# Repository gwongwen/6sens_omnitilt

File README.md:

# 6Sens: inSitu Seismic System for Slope Stability Sensing

## Desciption
The goal is to develop a warning system on the analysis of the evolution of the micro-seismic activity generated before the instability is triggered. The method uses a multitude of low-cost seismic sensors deployed in-situ in a network over the possibly unstable zone. The goal is to characterize the temporal evolution of seismic signals detected simultaneously by several sensors (i .e., co-detection). This method uses to its advantage the heterogeneity of the materials and the attenuation of the waves during their propagation in the material.

The design of these sensors is subject to certain technical constraints essential to good
operation of the project:

    - Be autonomous in energy, over a period of several months (so as not to have to return to site, often dangerous).
    - Be robust, reliable and adapted to extreme climatic conditions (cold, hot, humidity).
    - All sensors in the network must be synchronized precisely enough to perform the analysis (about 1/10 second).
    - Be able to communicate information in real time – or near – measurements to a gateway that will retransmit the data to a dedicated website.
    - Be produced at low cost (to install a large-scale network, and have the possibility of to install sensors in hazardous areas with the possibility of losing them).

## Hardware description
### Geophone sensor
The choice fell on omni geometric sensors from Geospace Technologies such Omni-X-LT or GS-ONE. Seismic geophone is a type of sensor that converts ground movement or a kind vibration into voltage, which could be acquired by an acquisition system. The deviation of this mesured voltage from the base line is called the geophone response and is analysed and for monitoring vibration generated by nature in our case.

The frequency response of the geophone is a kind of harmonic oscillator, which is deternined by corner frequency, around 15Hz for the chosen sensors and damping (typically 0.7 for our case).
Our application require the full wave to be sued and the three-component 3C geophones is used (Omni-X-LT or GS-ONE).
For more information, please to refer to : https://www.geospace.com/products/sensors/

### Amplification/Filtering board
The specifications inform us about the bandwidth of the filtering to be carried out: from 20Hz at 100Hz. So we have to build a band-pass filter having an amplification almost constant on this band and rejects frequencies outside this band. Moreover, the signal will have to be amplified in order to obtain a complete dynamic range between 0 and 3.3V without saturation. Below are listed the
parameters of the different filters that will make up the amplification and filtering card :

    - Filter 1 : active bandpass filter, gain : 33dB, low frequency : 7Hz, high frequency : 154Hz
    - Filter 2 : passive low-pass filter, no gain, cut frequency : 106Hz
    - Filter 3 : active low-pass filter, gain : 6dB, cut frequency : 234Hz

### CPU/Radio board for test
The choice fell on Cicerone MKR main board. Move-X Cicerone LoRa/GNSS Board is a high-performance, low-power, Arduino MKR-compatible development board based on the MAMWLE LoRa Module and the u-blox MAX-M10S GNSS Module. The Cicerone Board delivers best-in-class GNSS, long-range wireless connection, and high-performance MCU processing in a low-power solution for optimal battery life. The Cicerone Board allows users to build tracking applications worldwide with meter-level accuracy and to communicate long-range, low-power data via LoRaWAN. The integrated Li-Po charging circuit enables the Cicerone Board to manage battery charging through the USB port.

### CPU/Radio board for POC
The choice was made to manufacture our own PCB. It has three parts: the MAMWLE-01 radio chipset to transmit LoRaWAN packets (based on an STM32WLE5jx), a UWB chipset DW1000 to measure distance between two sensors and an analog part to supply radio chipset (solar panel or/and Li-Po battery). Connectors (Arduino MKR-compatible) have also been added to insert the seismic sensor amplification/filtering board.

## Firmware description
For this project, the use of Zephyr RTOS has been retained. To see what is Zephyr RTOS and how to install it on your computer, go to https://docs.zephyrproject.org/latest/develop/getting_started/index.html (it supports Linux OS, Windows OS and macOS).

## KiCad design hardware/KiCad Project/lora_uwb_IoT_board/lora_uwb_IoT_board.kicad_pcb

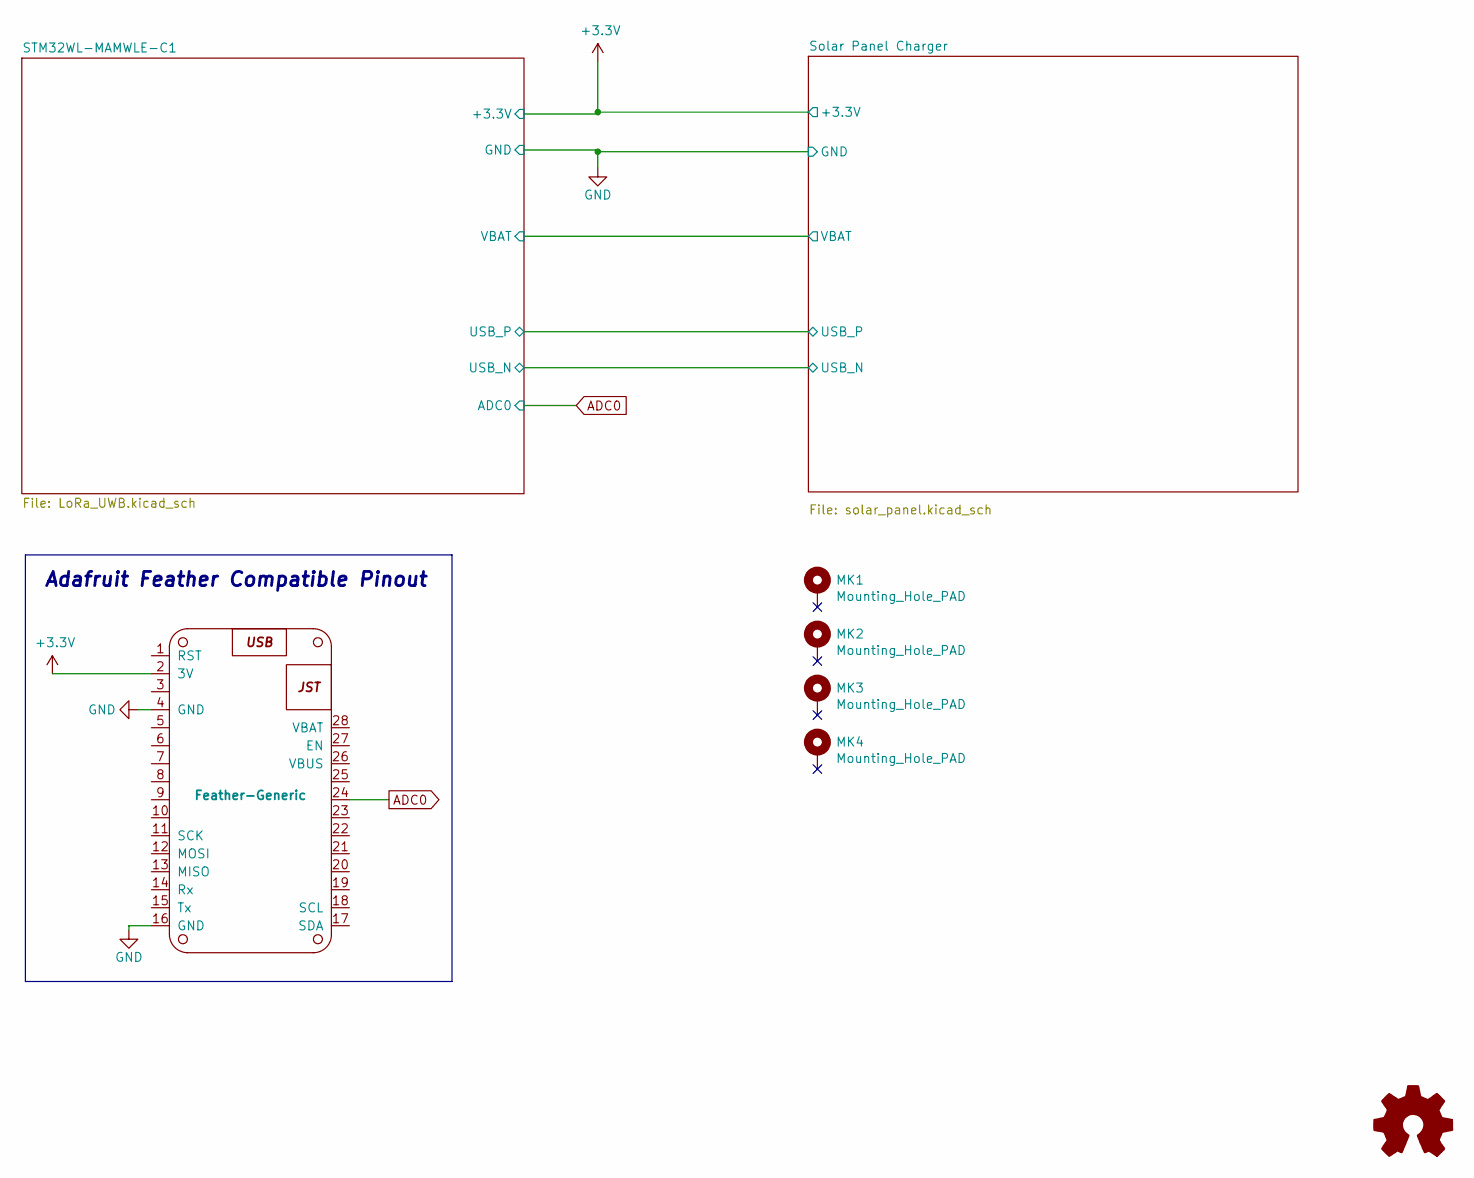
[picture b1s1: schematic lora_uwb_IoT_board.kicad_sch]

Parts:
MK1, MK2, MK3, MK4: Mounting_Hole_PAD; MountingHole_2.7mm
U300: Feather-Generic; Feather-Generic-no-holes

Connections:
+3V3: U300.2 (3V); also elsewhere on the board
ADC0: U300.24; also elsewhere on the board
GND: U300.4 (GND), U300.16 (GND); also elsewhere on the board

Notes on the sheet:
Adafruit Feather Compatible Pinout

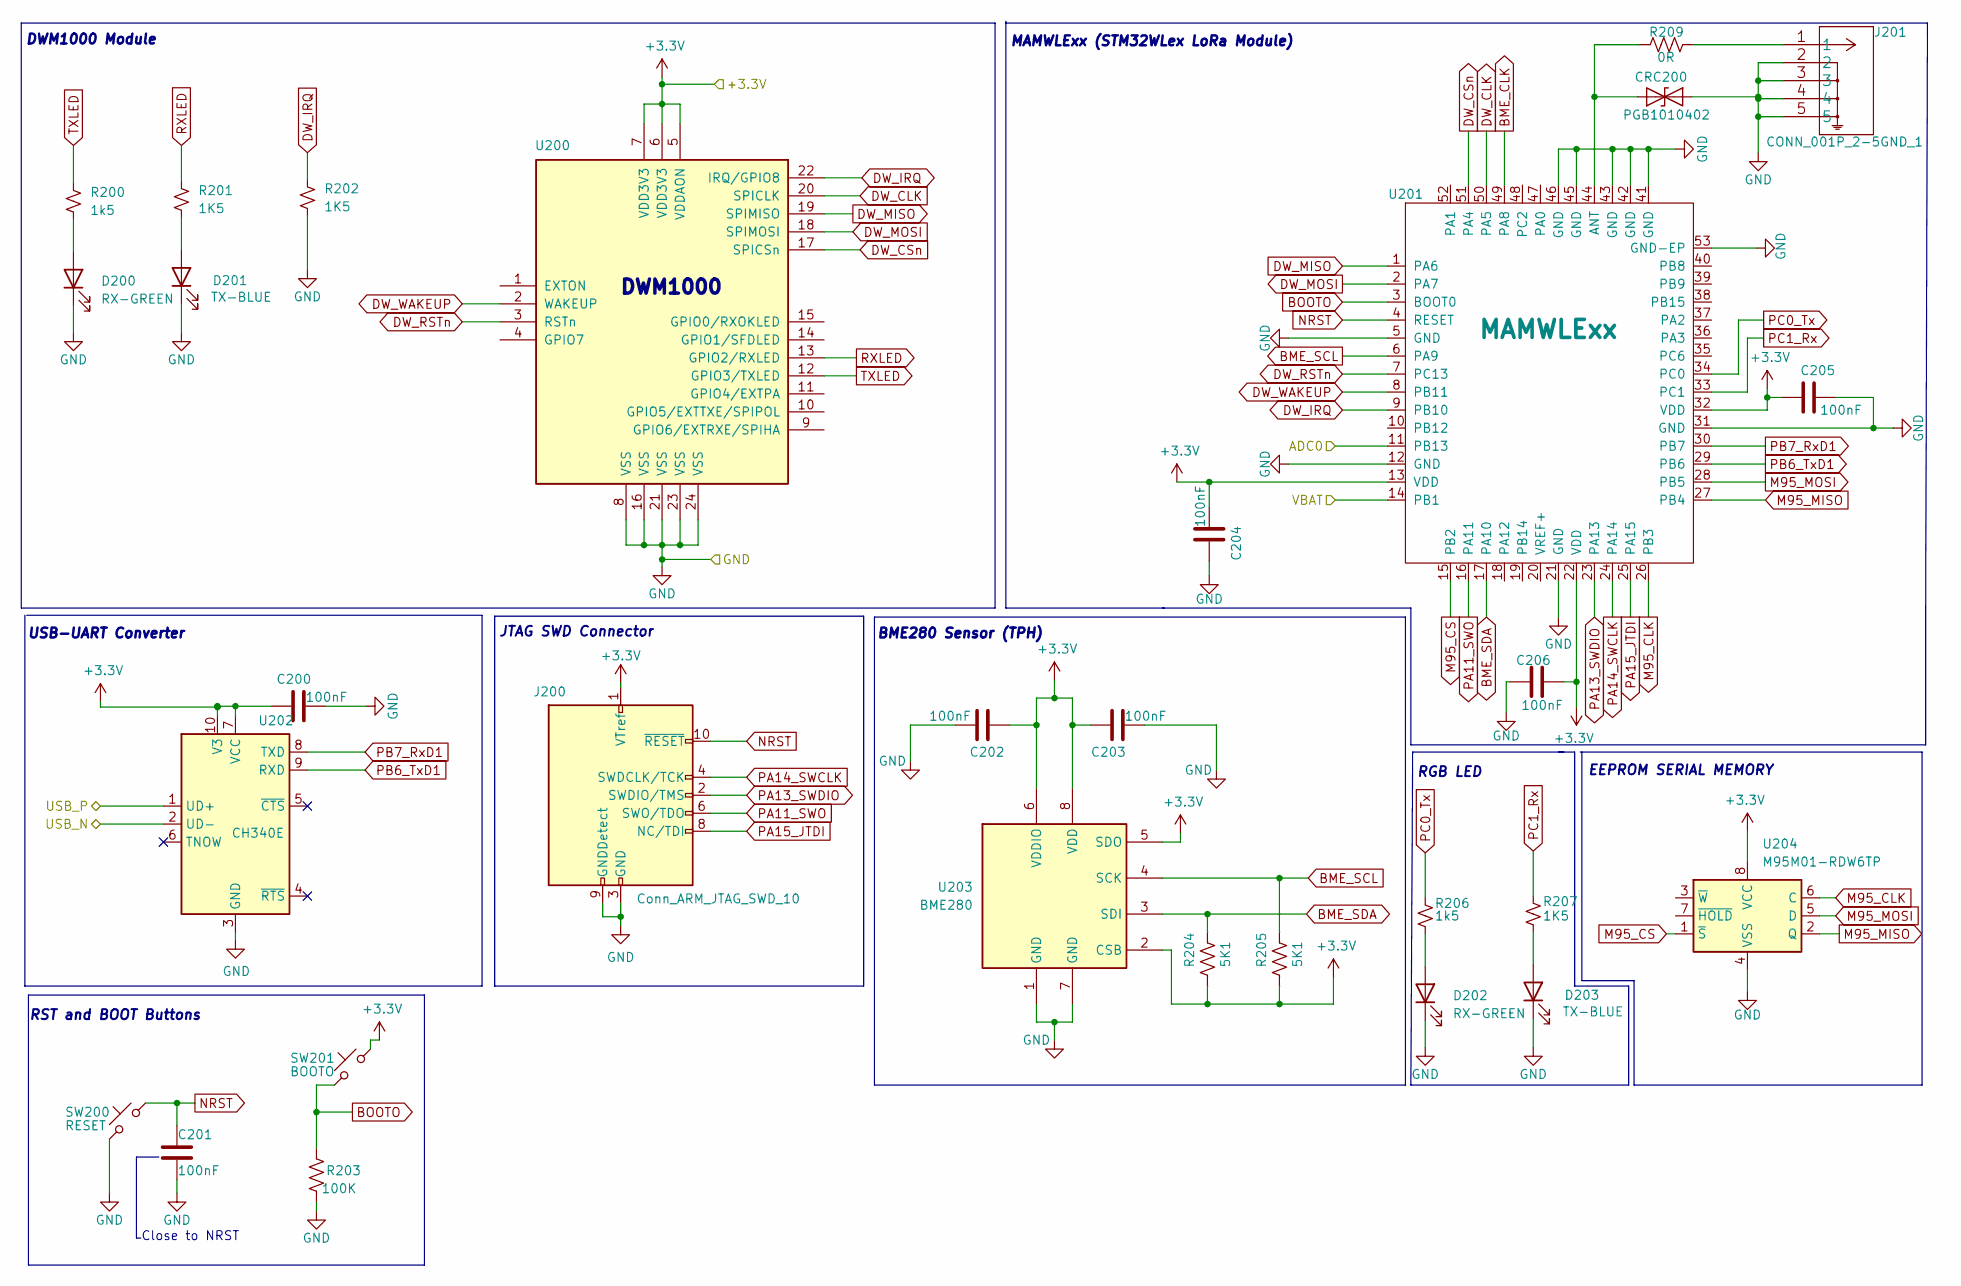
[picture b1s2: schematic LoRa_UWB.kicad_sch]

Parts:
C200, C201, C202, C203, C204, C205, C206: 100nF; C_0402_1005Metric; MPN GRM155R61A104KA01D
CRC200: PGB1010402; PGB1010402KR; MPN PGB1010402KR
D200, D202: RX-GREEN; LED_0603_1608Metric; MPN LTST-C191KGKT
D201, D203: TX-BLUE; LED_0603_1608Metric; MPN LTST-C191TBKT
J200: Conn_ARM_JTAG_SWD_10; PinHeader_2x05_P1.27mm_Vertical_SMD; MPN 20021121-00010C4LF
J201: CONN_001P_2-5GND_1; 142-0701-851; MPN 142-0701-851
R200, R206: 1k5; R_0402_1005Metric; MPN RC0402JR-071K5L
R201, R202, R207: 1K5; R_0402_1005Metric; MPN RC0402JR-071K5L
R203: 100K; R_0402_1005Metric; MPN RC0402JR-07100KL
R204, R205: 5K1; R_0402_1005Metric; MPN RC0402FR-075K1L
R209: 0R; R_0402_1005Metric; MPN RC0402JR-070RL
SW200: RESET; SW_Push_1P1T_NO_Vertical_Wuerth_434133025816; MPN 434133025816
SW201: BOOTO; SW_Push_1P1T_NO_Vertical_Wuerth_434133025816; MPN 434133025816
U200: DWM1000; MPN DWM1000
U201: MAMWLExx; MPN MAMWLE-01
U202: CH340E; MSOP-10_3x3mm_P0.5mm; MPN COM-16278
U203: BME280; Bosch_LGA-8_2.5x2.5mm_P0.65mm_ClockwisePinNumbering; MPN 828-1063-2-ND
U204: M95M01-RDW6TP; TSSOP-8_4.4x3mm_P0.65mm

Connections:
+3V3: C200.1, C202.1, C203.1, C204.2, C205.2, C206.1, J200.1 (VTref), R204.2, R205.2, SW201.2, U200.5 (VDDAON), U200.6 (VDD3V3), U200.7 (VDD3V3), U201.13 (VDD), U201.22 (VDD), U201.32 (VDD), U202.7 (VCC), U202.10 (V3), U203.2 (CSB), U203.5 (SDO), U203.6 (VDDIO), U203.8 (VDD), U204.8 (VCC); also elsewhere on the board
/STM32WL-MAMWLE-C1/USB_N: U202.2 (UD-); also elsewhere on the board
/STM32WL-MAMWLE-C1/USB_P: U202.1 (UD+); also elsewhere on the board
ADC0: U201.11 (PB13); also elsewhere on the board
BME_CLK: U201.49 (PA8)
BME_SCL: R205.1, U201.6 (PA9), U203.4 (SCK)
BME_SDA: R204.1, U201.17 (PA10), U203.3 (SDI)
BOOTO: R203.1, SW201.1, U201.3 (BOOT0)
DW_CLK: U200.20 (SPICLK), U201.50 (PA5)
DW_CSn: U200.17 (SPICSn), U201.51 (PA4)
DW_IRQ: R202.1, U200.22 (IRQ/GPIO8), U201.9 (PB10)
DW_MISO: U200.19 (SPIMISO), U201.1 (PA6)
DW_MOSI: U200.18 (SPIMOSI), U201.2 (PA7)
DW_RSTn: U200.3 (RSTn), U201.7 (PC13)
DW_WAKEUP: U200.2 (WAKEUP), U201.8 (PB11)
GND: C200.2, C201.2, C202.2, C203.2, C204.1, C205.1, C206.2, CRC200.2 (A2), D200.1 (K), D201.1 (K), D202.1 (K), D203.1 (K), J200.3 (GND), J200.5 (GND), J200.9 (GNDDetect), J201.2, J201.3, J201.4, J201.5, R202.2, R203.2, SW200.1, U200.8 (VSS), U200.16 (VSS), U200.21 (VSS), U200.23 (VSS), U200.24 (VSS), U201.5 (GND), U201.12 (GND), U201.21 (GND), U201.31 (GND), U201.41 (GND), U201.42 (GND), U201.43 (GND), U201.45 (GND), U201.46 (GND), U201.53 (GND-EP), U201.54 (GND-EP), U201.55 (GND-EP), U201.56 (GND-EP), U201.57 (GND-EP), U201.58 (GND-EP), U201.59 (GND-EP), U201.60 (GND-EP), U201.61 (GND-EP), U201.62 (GND-EP), U201.63 (GND-EP), U201.64 (GND-EP), U201.65 (GND-EP), U201.66 (GND-EP), U202.3 (GND), U203.1 (GND), U203.7 (GND), U204.4 (VSS); also elsewhere on the board
M95_CLK: U201.26 (PB3), U204.6 (C)
M95_CS: U201.15 (PB2), U204.1 (~S)
M95_MISO: U201.27 (PB4), U204.2 (Q)
M95_MOSI: U201.28 (PB5), U204.5 (D)
NRST: C201.1, J200.10 (~RESET), SW200.2, U201.4 (RESET)
unnamed: CRC200.1 (A1), R209.1, U201.44 (ANT)
unnamed: D200.2 (A), R200.2
unnamed: D201.2 (A), R201.2
unnamed: J201.1, R209.2
unnamed: D202.2 (A), R206.2
unnamed: D203.2 (A), R207.2
PA11_SWO: J200.6 (SWO/TDO), U201.16 (PA11)
PA13_SWDIO: J200.2 (SWDIO/TMS), U201.23 (PA13)
PA14_SWCLK: J200.4 (SWDCLK/TCK), U201.24 (PA14)
PA15_JTDI: J200.8 (NC/TDI), U201.25 (PA15)
PB6_TxD1: U201.29 (PB6), U202.9 (RXD)
PB7_RxD1: U201.30 (PB7), U202.8 (TXD)
PC0_Tx: R206.1, U201.34 (PC0)
PC1_Rx: R207.1, U201.33 (PC1)
RXLED: R201.1, U200.13 (GPIO2/RXLED)
TXLED: R200.1, U200.12 (GPIO3/TXLED)
VBAT: U201.14 (PB1); also elsewhere on the board

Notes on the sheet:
DWM1000 Module
Close to NRST
DWM1000
RGB LED
JTAG SWD Connector
USB-UART Converter
BME280 Sensor (TPH)
MAMWLExx (STM32WLex LoRa Module)
RST and BOOT Buttons
EEPROM SERIAL MEMORY

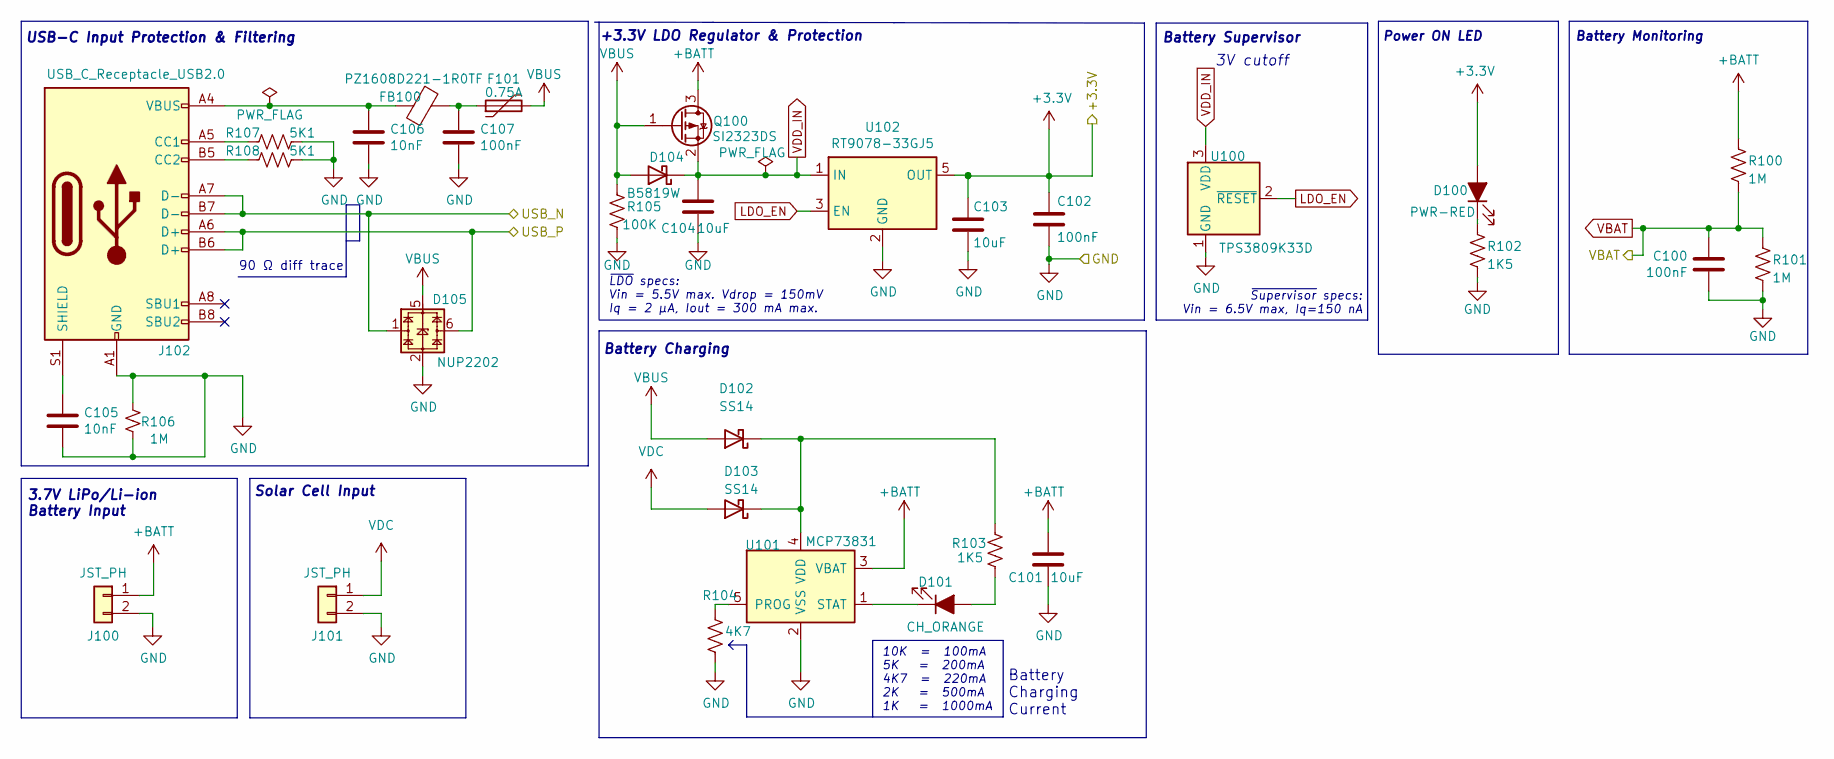
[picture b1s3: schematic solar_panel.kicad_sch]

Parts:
C100, C102, C107: 100nF; C_0402_1005Metric; MPN GRM155R61A104KA01D
C101, C103, C104: 10uF; C_0603_1608Metric; MPN GRT188C81A106ME13J
C105: 10nF; C_0402_1005Metric; MPN GRM155R61A103KA01D
C106: 10nF; C_0402_1005Metric; MPN GRM155R61A103KA01D; LCSC_Part# Murata Electronics
D100: PWR-RED; LED_0603_1608Metric; MPN LTST-C191KRKT
D101: CH_ORANGE; LED_0603_1608Metric; MPN LTST-C191KFKT
D102, D103: SS14; D_SMA; MPN SS14
D104: B5819W; D_SOD-123; MPN B5819W
D105: NUP2202; SOT-363_SC-70-6; MPN NUP2202W1T2G
F101: 0.75A; Fuse_0805_2012Metric; MPN SMD0805B075TF
FB100: PZ1608D221-1R0TF; L_0603_1608Metric; MPN HPZ1608D221-1R2TF
J100, J101: JST_PH; JST_PH_S2B-PH-SM4-TB_1x02-1MP_P2.00mm_Horizontal; MPN S2B-PH-SM4-TB(LF)(SN)
J102: USB_C_Receptacle_USB2.0; USB_C_Receptacle_Amphenol_12401548E4-2A; MPN 12401598E4#2A
Q100: SI2323DS; SOT-23; MPN SI2323DS-T1-GE3
R100, R101, R106: 1M; R_0402_1005Metric; MPN RC0402JR-071ML
R102, R103: 1K5; R_0402_1005Metric; MPN RC0402JR-071K5L
R104: 4K7; R_0402_1005Metric; MPN RC0402JR-074K7L
R105: 100K; R_0402_1005Metric; MPN RC0402JR-07100KL
R107, R108: 5K1; R_0402_1005Metric; MPN RC0402FR-075K1L
U100: TPS3809K33D; SOT-23; MPN TPS3809K33DBVRG4
U101: MCP73831; SOT-23-5; MPN MCP73831T-2ACI/OT
U102: RT9078-33GJ5; TSOT-23-5; MPN RT9078-33GJ5

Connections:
+3V3: C102.1, C103.1, D100.2 (A), U102.5 (OUT); also elsewhere on the board
+BATT: C101.1, J100.1, Q100.3 (D), R100.1, U101.3 (VBAT)
/STM32WL-MAMWLE-C1/USB_N: D105.1, J102.A7 (D-), J102.B7 (D-); also elsewhere on the board
/STM32WL-MAMWLE-C1/USB_P: D105.6, J102.A6 (D+), J102.B6 (D+); also elsewhere on the board
GND: C100.1, C101.2, C102.2, C103.2, C104.2, C105.1, C106.2, C107.2, D105.2, J100.2, J101.2, J102.A1 (GND), J102.A12 (GND), J102.B1 (GND), J102.B12 (GND), R101.2, R102.2, R104.2, R105.2, R106.1, R106.2, R107.1, R108.1, U100.1 (GND), U101.2 (VSS), U102.2 (GND); also elsewhere on the board
LDO_EN: U100.2 (~RESET), U102.3 (EN)
unnamed: C105.2, J102.S1 (SHIELD)
unnamed: C106.1, FB100.1, J102.A4 (VBUS), J102.A9 (VBUS), J102.B4 (VBUS), J102.B9 (VBUS)
unnamed: C107.1, F101.1, FB100.2
unnamed: D100.1 (K), R102.1
unnamed: D101.1 (K), U101.1 (STAT)
unnamed: D101.2 (A), R103.2
unnamed: D102.1 (K), D103.1 (K), R103.1, U101.4 (VDD)
unnamed: J102.A5 (CC1), R107.2
unnamed: J102.B5 (CC2), R108.2
unnamed: R104.1, U101.5 (PROG)
VBAT: C100.2, R100.2, R101.1; also elsewhere on the board
VBUS: D102.2 (A), D104.2 (A), D105.5, F101.2, Q100.1 (G), R105.1
VDC: D103.2 (A), J101.1
VDD_IN: C104.1, D104.1 (K), Q100.2 (S), U100.3 (VDD), U102.1 (IN)

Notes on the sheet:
3V cutoff
Solar Cell Input
90 Ω diff trace
+3.3V LDO Regulator & Protection
Battery Charging Current
10K = 100mA 5K = 200mA 4K7 = 220mA 2K = 500mA 1K = 1000mA
3.7V LiPo/Li-ion Battery Input
Battery Supervisor
Power ON LED
Battery Monitoring
~{Supervisor} specs: Vin = 6.5V max, Iq=150 nA
USB-C Input Protection & Filtering
~{LDO} specs: Vin = 5.5V max. Vdrop = 150mV Iq = 2 μA, Iout = 300 mA max.
Battery Charging

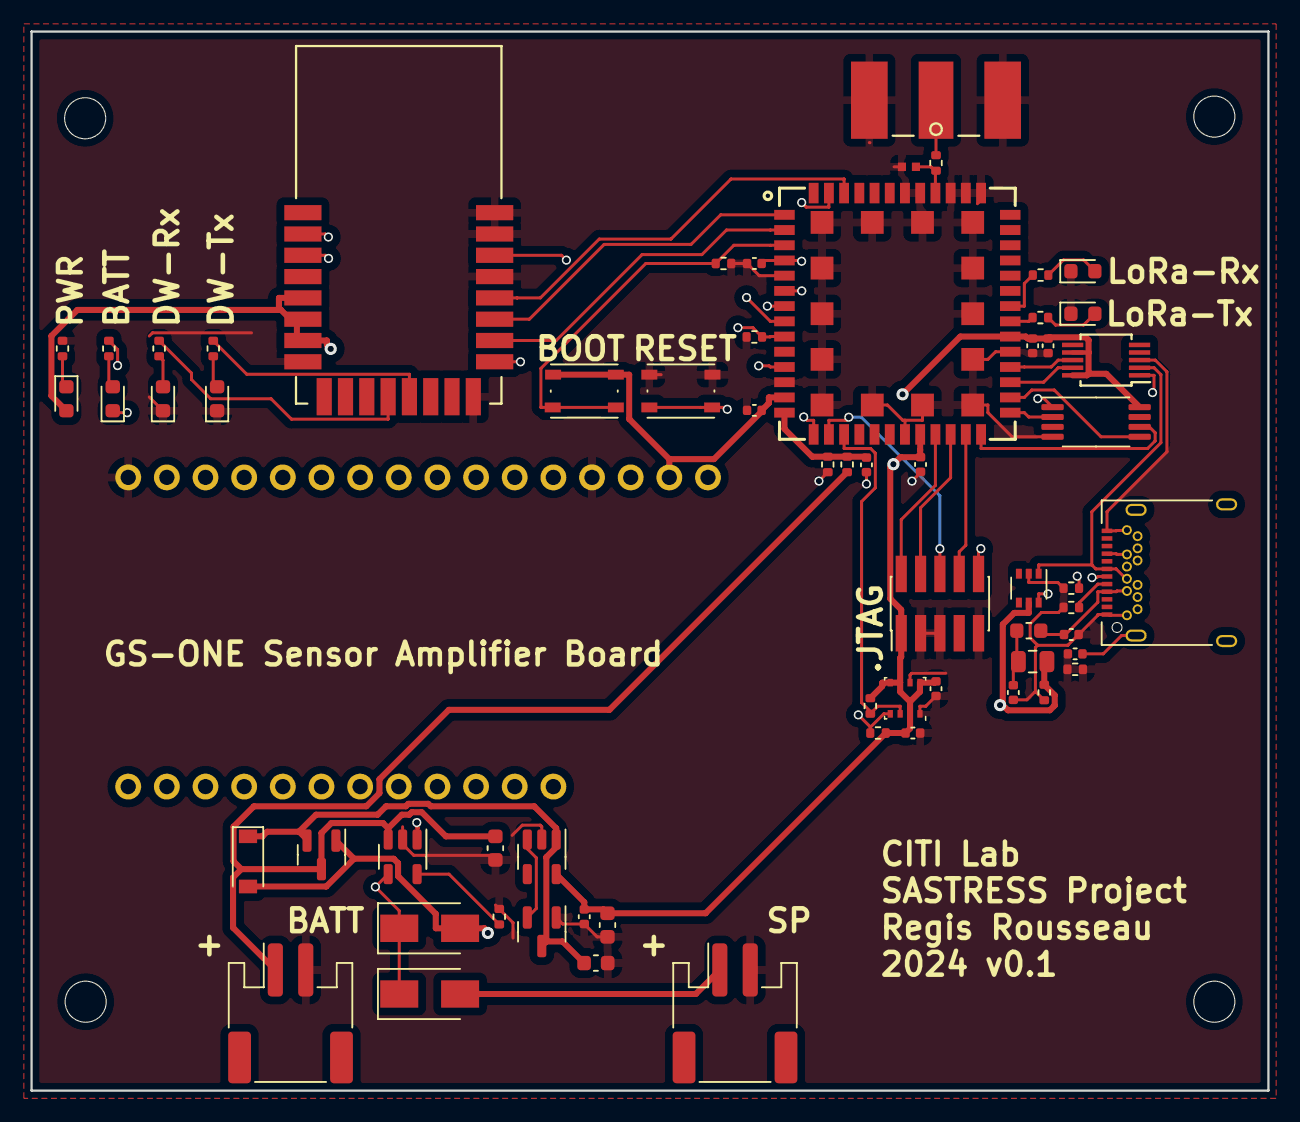
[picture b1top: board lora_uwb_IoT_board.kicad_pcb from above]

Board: 4 copper layers, 81.3 x 69.6 mm, 67 parts (0 on the bottom side), 52 nets.

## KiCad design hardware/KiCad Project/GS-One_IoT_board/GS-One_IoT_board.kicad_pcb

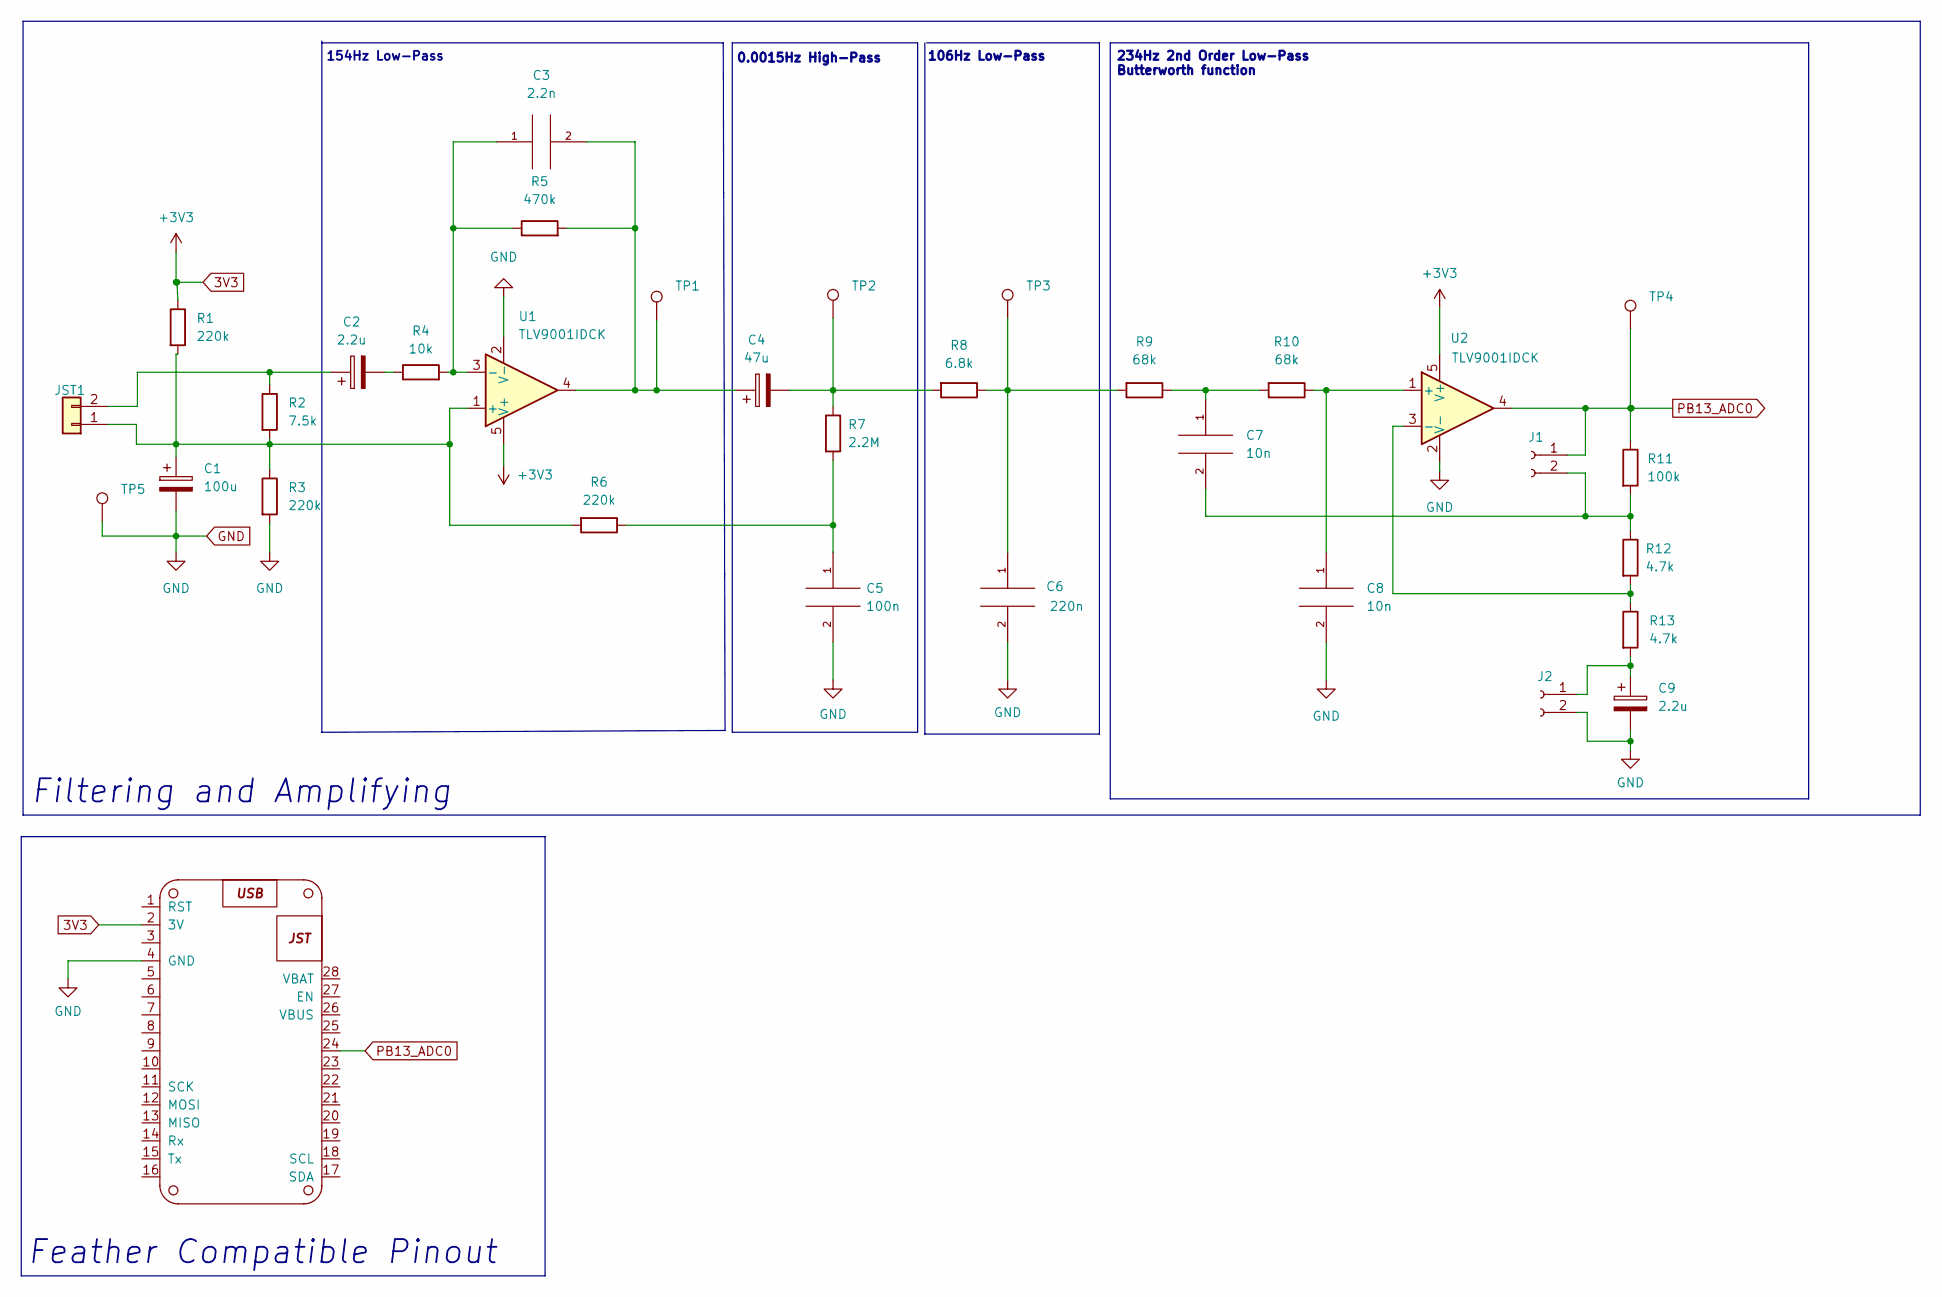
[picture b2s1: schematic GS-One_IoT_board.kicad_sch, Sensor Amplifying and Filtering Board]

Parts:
C1: 100u; C_1206_3216Metric; MPN GRM31CD80J107MEA8K
C2, C9: 2.2u; C_0603_1608Metric; MPN GRM188R61E106KA73J
C3: 2.2n; C_0805_2012Metric; MPN GCJ216R71H222KA01D
C4: 47u; C_0805_2012Metric; MPN GRM21BR61A476ME15K
C5: 100n; C_0603_1608Metric; MPN GCM188R91E104KA37J
C6: 220n; C_0603_1608Metric; MPN GCM188R71E224KA55J
C7, C8: 10n; C_0805_2012Metric; MPN GCM219R91H103KA37D
J1, J2: Conn_01x02_Female; PinHeader_1x02_P2.54mm_Vertical
JST1: Conn_01x02; JST_PH_B2B-PH-SM4-TB_1x02-1MP_P2.00mm_Vertical; MPN B2B-PH-SM4-TB(LF)(SN)
R1, R3, R6: 220k; R_0805_2012Metric; MPN ESR10EZPF2203
R2: 7.5k; R_0805_2012Metric; MPN ESR10EZPF7501
R4: 10k; R_0805_2012Metric; MPN ESR10EZPF1002
R5: 470k; R_0805_2012Metric; MPN ESR10EZPF4703
R7: 2.2M; R_0805_2012Metric; MPN ESR10EZPF2204
R8: 6.8k; R_0805_2012Metric; MPN ESR10EZPF6801
R9, R10: 68k; R_0805_2012Metric; MPN ESR10EZPF6802
R11: 100k; R_0805_2012Metric; MPN ESR10EZPF1003
R12, R13: 4.7k; R_0805_2012Metric; MPN ESR10EZPF4701
TP1, TP2, TP3, TP4, TP5: TestPoint; TestPoint_Keystone_5015_Micro-Minature; MPN 36-5015TR-ND
U1, U2: TLV9001IDCK; SOT-353_SC-70-5; MPN TLV9001IDCKR
board1: Feather-Generic; Feather-Generic-no-holes

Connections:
3V3: R1.1, U1.5 (V+), U2.5 (V+), board1.2 (3V)
GND: C1.2, C5.2, C6.2, C8.2, C9.2, J2.2, R3.2, TP5.1, U1.2 (V-), U2.2 (V-), board1.4 (GND)
unnamed: C1.1, JST1.1, R1.2, R2.2, R3.1, R6.2, U1.1 (+)
unnamed: C2.1, JST1.2, R2.1
unnamed: C2.2, R4.1
unnamed: C3.1, R4.2, R5.1, U1.3 (-)
unnamed: C3.2, C4.1, R5.2, TP1.1, U1.4
unnamed: C4.2, R7.1, R8.2, TP2.1
unnamed: C5.1, R6.1, R7.2
unnamed: C6.1, R8.1, R9.2, TP3.1
unnamed: C7.1, R9.1, R10.2
unnamed: C7.2, J1.2, R11.2, R12.1
unnamed: C8.1, R10.1, U2.1 (+)
unnamed: C9.1, J2.1, R13.2
unnamed: R12.2, R13.1, U2.3 (-)
PB13_ADC0: J1.1, R11.1, TP4.1, U2.4, board1.24

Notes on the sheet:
0.0015Hz High-Pass
Feather Compatible Pinout
Filtering and Amplifying
154Hz Low-Pass
106Hz Low-Pass
234Hz 2nd Order Low-Pass Butterworth function

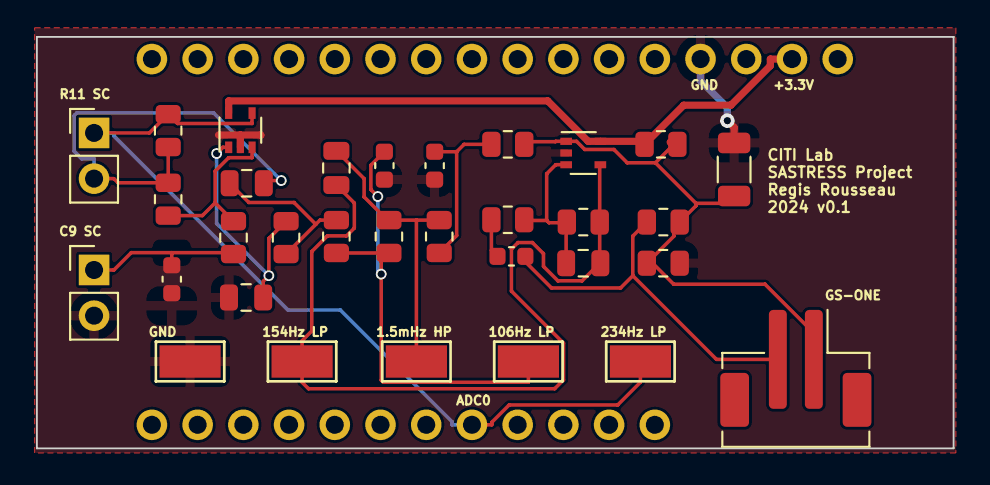
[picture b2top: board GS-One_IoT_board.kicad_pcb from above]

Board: 2 copper layers, 50.9 x 22.9 mm, 33 parts (0 on the bottom side), 16 nets.

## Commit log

2023-02-24 add description and KiCad project files
2023-02-27 add description of project
2023-03-03 update KiCad files
2023-03-03 update KiCad photos
2023-03-03 add information to geophone sensor
2023-03-03 add description about CPU board
2023-03-03 initilaize platformio
2023-03-09 update to zephyr RTOS framework
2023-03-09 add ADS1110 (TI's ADC) Driver
2023-03-09 first code for ADC test
2023-04-07 update KiCAD project and datasheet
2023-04-24 add comments on readme file
2023-06-20 complete overhaul of project
2023-06-23 add VBAT test in main function (stm32_adc)
2023-06-23 add comment on board overlay file
2023-06-23 add BME280 driver in overlay file for future instance
2023-06-23 add comment on readme file
2023-06-26 add firmware part on readme file
2023-06-26 bug fixes
2023-11-22 inititialize new firmware
2023-12-06 add nvs delete interrupt one per day
2023-12-06 add separated function for nvs deleted per day
2023-12-08 concatenate bme value
2023-12-20 bug fixes in interrupt routine
2024-01-23 final version v0.1 for hardware
2024-01-30 update kicad pcb
